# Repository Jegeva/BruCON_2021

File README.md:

BruCON 2021
=
This is the firmware and pcb for brucon badge 

as of released at the conference **ie. including** :

* the mistake that needs a bodge (vbat to the sensor, backlights and leds missing a bit of trace) and 
* the mistake with the connector (don't use the one refed in the kicad docs, it is keyed down instead of up)

Licenses :
=

-my (**ugly**) firmware code and the PCB are CERN-OHL-P

-the gasmask art is CC/NA by Ray Harvey

-Espressif stuff : 
[see here](https://docs.espressif.com/projects/esp-idf/en/latest/esp32/COPYRIGHT.html)

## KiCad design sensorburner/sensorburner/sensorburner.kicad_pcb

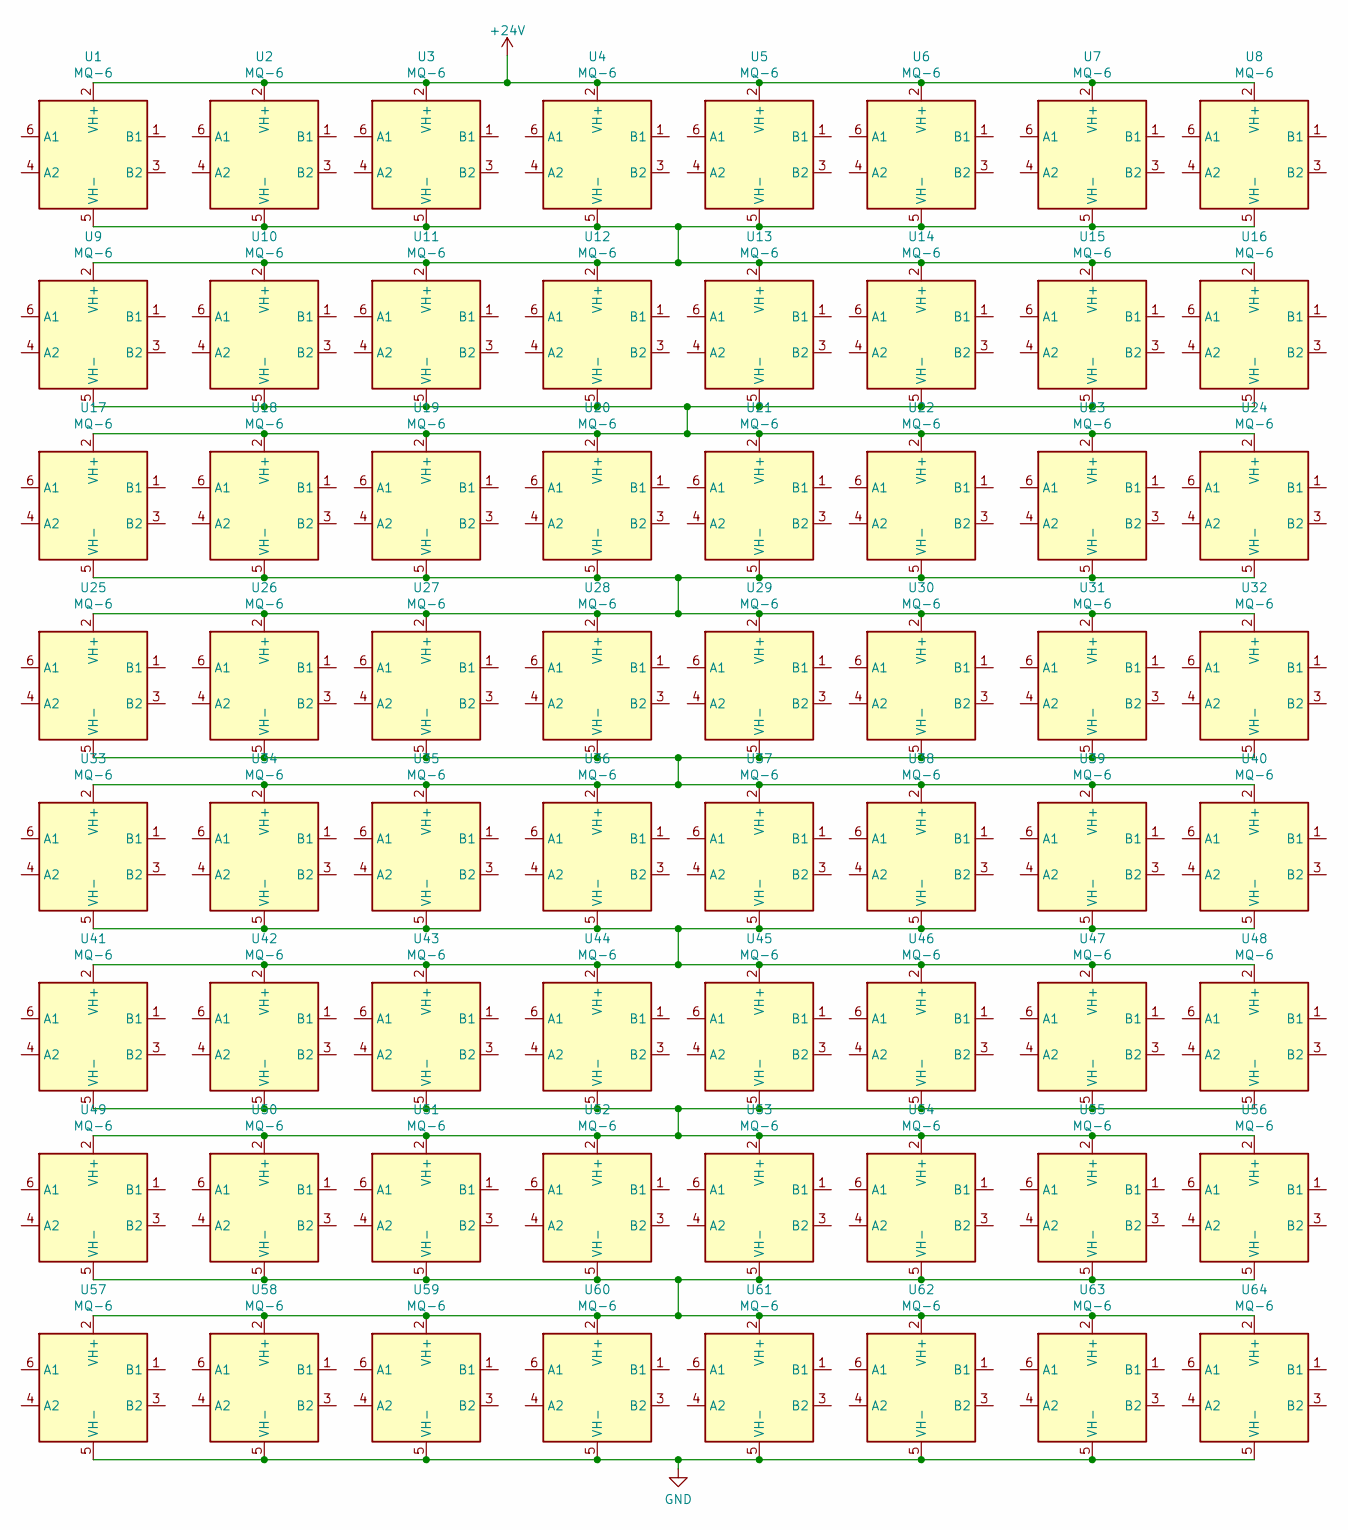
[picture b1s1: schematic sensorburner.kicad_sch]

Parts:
U1, U2, U3, U4, U5, U6, U7, U8, U9, U10, U11, U12, U13, U14, U15, U16, U17, U18, U19, U20, U21, U22, U23, U24, U25, U26, U27, U28, U29, U30, U31, U32, U33, U34, U35, U36, U37, U38, U39, U40, U41, U42, U43, U44, U45, U46, U47, U48, U49, U50, U51, U52, U53, U54, U55, U56, U57, U58, U59, U60, U61, U62, U63, U64: MQ-6; MQ-3-sparkfuntight

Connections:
+24V: U1.2 (VH+), U2.2 (VH+), U3.2 (VH+), U4.2 (VH+), U5.2 (VH+), U6.2 (VH+), U7.2 (VH+), U8.2 (VH+)
GND: U57.5 (VH-), U58.5 (VH-), U59.5 (VH-), U60.5 (VH-), U61.5 (VH-), U62.5 (VH-), U63.5 (VH-), U64.5 (VH-)
unnamed: U1.5 (VH-), U2.5 (VH-), U3.5 (VH-), U4.5 (VH-), U5.5 (VH-), U6.5 (VH-), U7.5 (VH-), U8.5 (VH-), U9.2 (VH+), U10.2 (VH+), U11.2 (VH+), U12.2 (VH+), U13.2 (VH+), U14.2 (VH+), U15.2 (VH+), U16.2 (VH+)
unnamed: U9.5 (VH-), U10.5 (VH-), U11.5 (VH-), U12.5 (VH-), U13.5 (VH-), U14.5 (VH-), U15.5 (VH-), U16.5 (VH-), U17.2 (VH+), U18.2 (VH+), U19.2 (VH+), U20.2 (VH+), U21.2 (VH+), U22.2 (VH+), U23.2 (VH+), U24.2 (VH+)
unnamed: U17.5 (VH-), U18.5 (VH-), U19.5 (VH-), U20.5 (VH-), U21.5 (VH-), U22.5 (VH-), U23.5 (VH-), U24.5 (VH-), U25.2 (VH+), U26.2 (VH+), U27.2 (VH+), U28.2 (VH+), U29.2 (VH+), U30.2 (VH+), U31.2 (VH+), U32.2 (VH+)
unnamed: U25.5 (VH-), U26.5 (VH-), U27.5 (VH-), U28.5 (VH-), U29.5 (VH-), U30.5 (VH-), U31.5 (VH-), U32.5 (VH-), U33.2 (VH+), U34.2 (VH+), U35.2 (VH+), U36.2 (VH+), U37.2 (VH+), U38.2 (VH+), U39.2 (VH+), U40.2 (VH+)
unnamed: U33.5 (VH-), U34.5 (VH-), U35.5 (VH-), U36.5 (VH-), U37.5 (VH-), U38.5 (VH-), U39.5 (VH-), U40.5 (VH-), U41.2 (VH+), U42.2 (VH+), U43.2 (VH+), U44.2 (VH+), U45.2 (VH+), U46.2 (VH+), U47.2 (VH+), U48.2 (VH+)
unnamed: U41.5 (VH-), U42.5 (VH-), U43.5 (VH-), U44.5 (VH-), U45.5 (VH-), U46.5 (VH-), U47.5 (VH-), U48.5 (VH-), U49.2 (VH+), U50.2 (VH+), U51.2 (VH+), U52.2 (VH+), U53.2 (VH+), U54.2 (VH+), U55.2 (VH+), U56.2 (VH+)
unnamed: U49.5 (VH-), U50.5 (VH-), U51.5 (VH-), U52.5 (VH-), U53.5 (VH-), U54.5 (VH-), U55.5 (VH-), U56.5 (VH-), U57.2 (VH+), U58.2 (VH+), U59.2 (VH+), U60.2 (VH+), U61.2 (VH+), U62.2 (VH+), U63.2 (VH+), U64.2 (VH+)

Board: 2 copper layers, 64 parts (0 on the bottom side), 9 nets, no tracks yet.

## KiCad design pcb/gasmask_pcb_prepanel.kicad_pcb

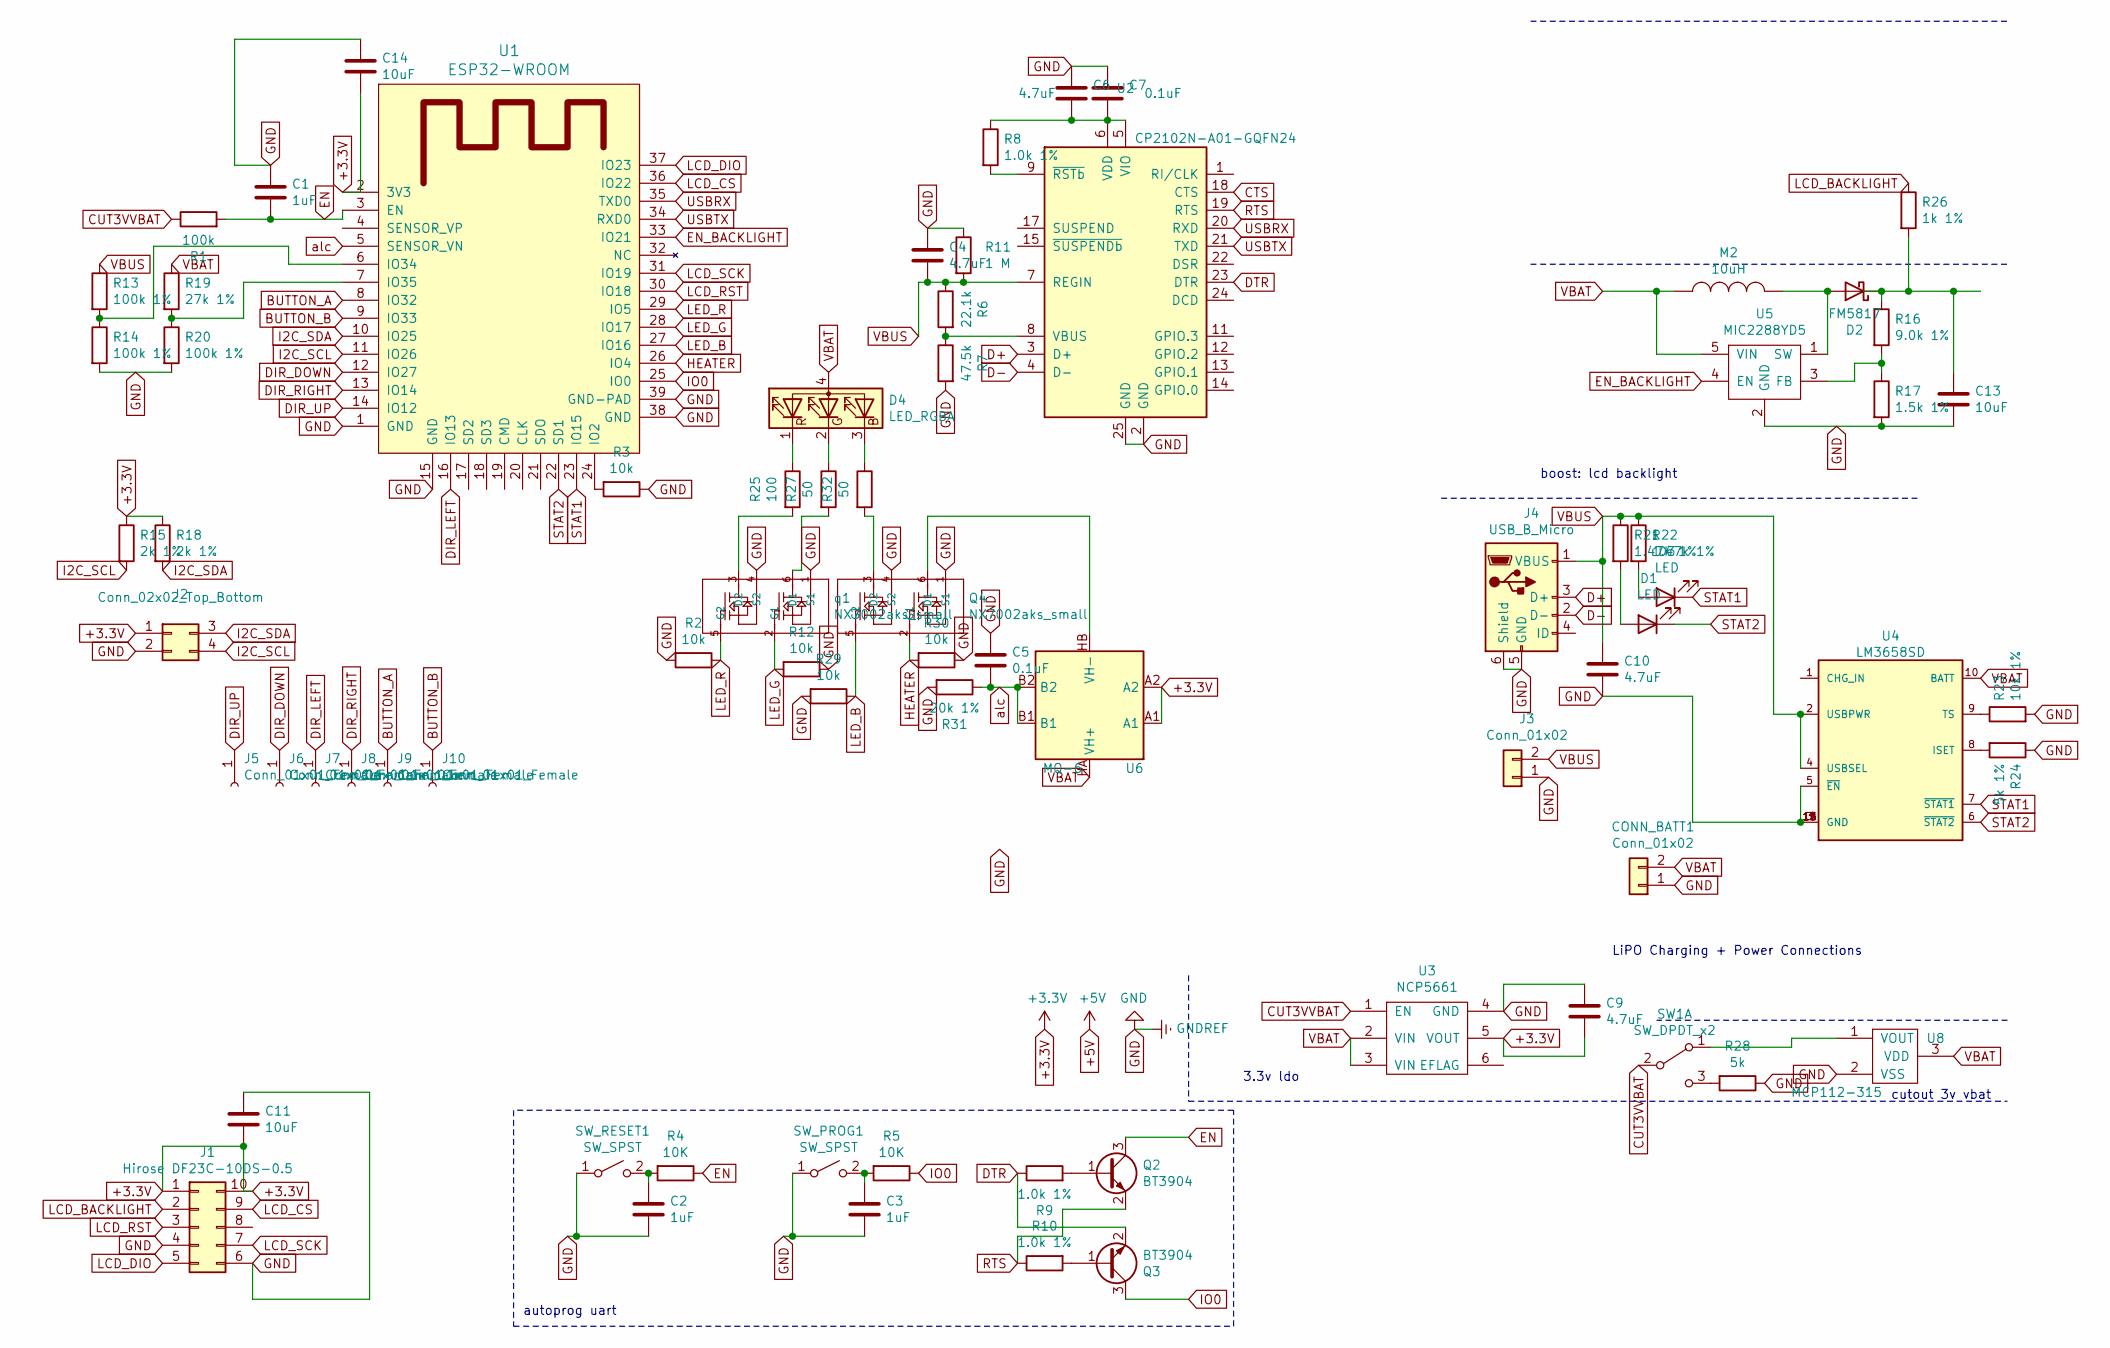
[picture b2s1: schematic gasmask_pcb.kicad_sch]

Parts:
C1, C2, C3: 1uF; C_0805_2012Metric
C4, C6, C9, C10: 4.7uF; C_0805_2012Metric
C5, C7: 0.1uF; C_0805_2012Metric
C11, C13, C14: 10uF; C_0805_2012Metric
CONN_BATT1: Conn_01x02; JST-PH-SM4-TB-2
D1, D3: LED; LED_0603_1608Metric
D2: FM5817; DO-214-FM5817
D4: LED_RGBA; LED_Cree-PLCC4_2x2mm_CW
J1: Hirose DF23C-10DS-0.5; DF23C-10DS-0.5V
J2: Conn_02x02_Top_Bottom; PinHeader_2x02_P2.54mm_Vertical
J3: Conn_01x02; PinHeader_1x02_P2.54mm_Vertical
J4: USB_B_Micro; USB_Micro-B_Molex_47346-0001
J5, J6, J7, J8, J9, J10: Conn_01x01_Female; touch_10mm
M2: 10uH; L_0805_2012Metric
Q2, Q3: BT3904; SOT-23
Q4: NX7002aks_small; SOT-363_SC-70-6
R1: 100k; R_0805_2012Metric
R2, R3, R12, R29, R30: 10k; R_0805_2012Metric
R4, R5: 10K; R_0805_2012Metric
R6: 22.1k; R_0805_2012Metric
R7: 47.5k; R_0805_2012Metric
R8, R9, R10: 1.0k 1%; R_0805_2012Metric
R11: 1 M; R_0805_2012Metric
R13, R14, R20: 100k 1%; R_0805_2012Metric
R15, R18: 2k 1%; R_0805_2012Metric
R16: 9.0k 1%; R_0805_2012Metric
R17: 1.5k 1%; R_0805_2012Metric
R19: 27k 1%; R_0805_2012Metric
R21, R22: 1.47k 1%; R_0805_2012Metric
R23: 10k 1%; R_0805_2012Metric
R24: 5k 1%; R_0805_2012Metric
R25: 100; R_0805_2012Metric
R26: 1k 1%; R_0805_2012Metric
R27, R32: 50; R_0805_2012Metric
R28: 5k; R_0805_2012Metric
R31: 20k 1%; R_0805_2012Metric
SW1: SW_DPDT_x2; JS102000-SAQN
SW_PROG1: SW_SPST; FSM4JSMATR
SW_RESET1: SW_SPST; FSM4JSMATR
U1: ESP32-WROOM
U2: CP2102N-A01-GQFN24; QFN-24-1EP_4x4mm_P0.5mm_EP2.6x2.6mm
U3: NCP5661; DFN6-3.6x2.15mmP0.95
U4: LM3658SD; IC_TPS61087DSCR
U5: MIC2288YD5; SOT-23-5
U6: MQ-6; MQ-3
U8: MCP112-315; SOT-23
q1: NX7002aks_small; SOT-363_SC-70-6

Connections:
+3.3V: C9.2, C11.2, C14.2, J1.1, J1.10, J2.1, R15.1, R18.1, U1.2 (3V3), U3.5 (VOUT), U6.A1, U6.A2
BUTTON_A: J9.1, U1.8 (IO32)
BUTTON_B: J10.1, U1.9 (IO33)
CTS: U2.18 (CTS)
CUT3VVBAT: R1.1, SW1.2 (B), U3.1 (EN)
D+: J4.3 (D+), U2.3 (D+)
D-: J4.2 (D-), U2.4 (D-)
DIR_DOWN: J6.1, U1.12 (IO27)
DIR_LEFT: J7.1, U1.16 (IO13)
DIR_RIGHT: J8.1, U1.13 (IO14)
DIR_UP: J5.1, U1.14 (IO12)
DTR: Q3.2 (E), R9.1, U2.23 (DTR)
EN: C1.2, Q2.3 (C), R1.2, R4.1, U1.3 (EN)
EN_BACKLIGHT: U1.33 (IO21), U5.4 (EN)
HEATER: Q4.2 (G1), R30.2, U1.26 (IO4)
I2C_SCL: J2.4, R15.2, U1.11 (IO26)
I2C_SDA: J2.3, R18.2, U1.10 (IO25)
IO0: Q3.3 (C), R5.1, U1.25 (IO0)
LCD_BACKLIGHT: J1.2, R26.1
LCD_CS: J1.9, U1.36 (IO22)
LCD_DIO: J1.5, U1.37 (IO23)
LCD_RST: J1.3, U1.30 (IO18)
LCD_SCK: J1.7, U1.31 (IO19)
LED_B: Q4.5 (G2), R29.1, U1.27 (IO16)
LED_G: R12.2, U1.28 (IO17), q1.2 (G1)
LED_R: R2.1, U1.29 (IO5), q1.5 (G2)
unnamed: C2.1, R4.2, SW_RESET1.2 (B)
unnamed: C3.1, R5.2, SW_PROG1.2 (B)
unnamed: C6.2, C7.2, R8.1, U2.5 (VIO), U2.6 (VDD)
unnamed: C13.1, D2.1 (K), R16.1, R26.2
unnamed: D1.2 (A), R21.2
unnamed: D2.2 (A), M2.2, U5.1 (SW)
unnamed: D3.2 (A), R22.2
unnamed: D4.1 (RK), R25.1
unnamed: D4.2 (GK), R27.1
unnamed: D4.3 (BK), R32.1
unnamed: Q2.1 (B), R9.2
unnamed: Q3.1 (B), R10.2
unnamed: Q4.3 (D2), R32.2
unnamed: Q4.6 (D1), U6.HB (VH-)
unnamed: R3.2, U1.24 (IO2)
unnamed: R6.2, R7.1, U2.8 (VBUS)
unnamed: R8.2, U2.9 (~RSTb)
unnamed: R13.2, R14.1, U1.6 (IO34)
unnamed: R16.2, R17.1, U5.3 (FB)
unnamed: R19.2, R20.1, U1.7 (IO35)
unnamed: R23.1, U4.9 (TS)
unnamed: R28.2, SW1.3 (C)
unnamed: SW1.1 (A), U8.1 (VOUT)
unnamed: R25.2, q1.3 (D2)
unnamed: R27.2, q1.6 (D1)
RTS: Q2.2 (E), R10.1, U2.19 (RTS)
STAT1: D3.1 (K), U1.23 (IO15), U4.7 (~STAT1)
STAT2: D1.1 (K), U1.22 (SD1), U4.6 (~STAT2)
USBRX: U1.35 (TXD0), U2.20 (RXD)
USBTX: U1.34 (RXD0), U2.21 (TXD)
VBAT: CONN_BATT1.2, D4.4 (A), M2.1, R19.1, U3.2 (VIN), U3.3 (VIN), U4.10 (BATT), U5.5 (VIN), U6.HA (VH+), U8.3 (VDD); also elsewhere on the board
alc: C5.2, R31.1, U1.5 (SENSOR_VN), U6.B1, U6.B2

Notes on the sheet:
autoprog uart
3.3v ldo
boost: lcd backlight
LiPO Charging + Power Connections
cutout 3v vbat

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
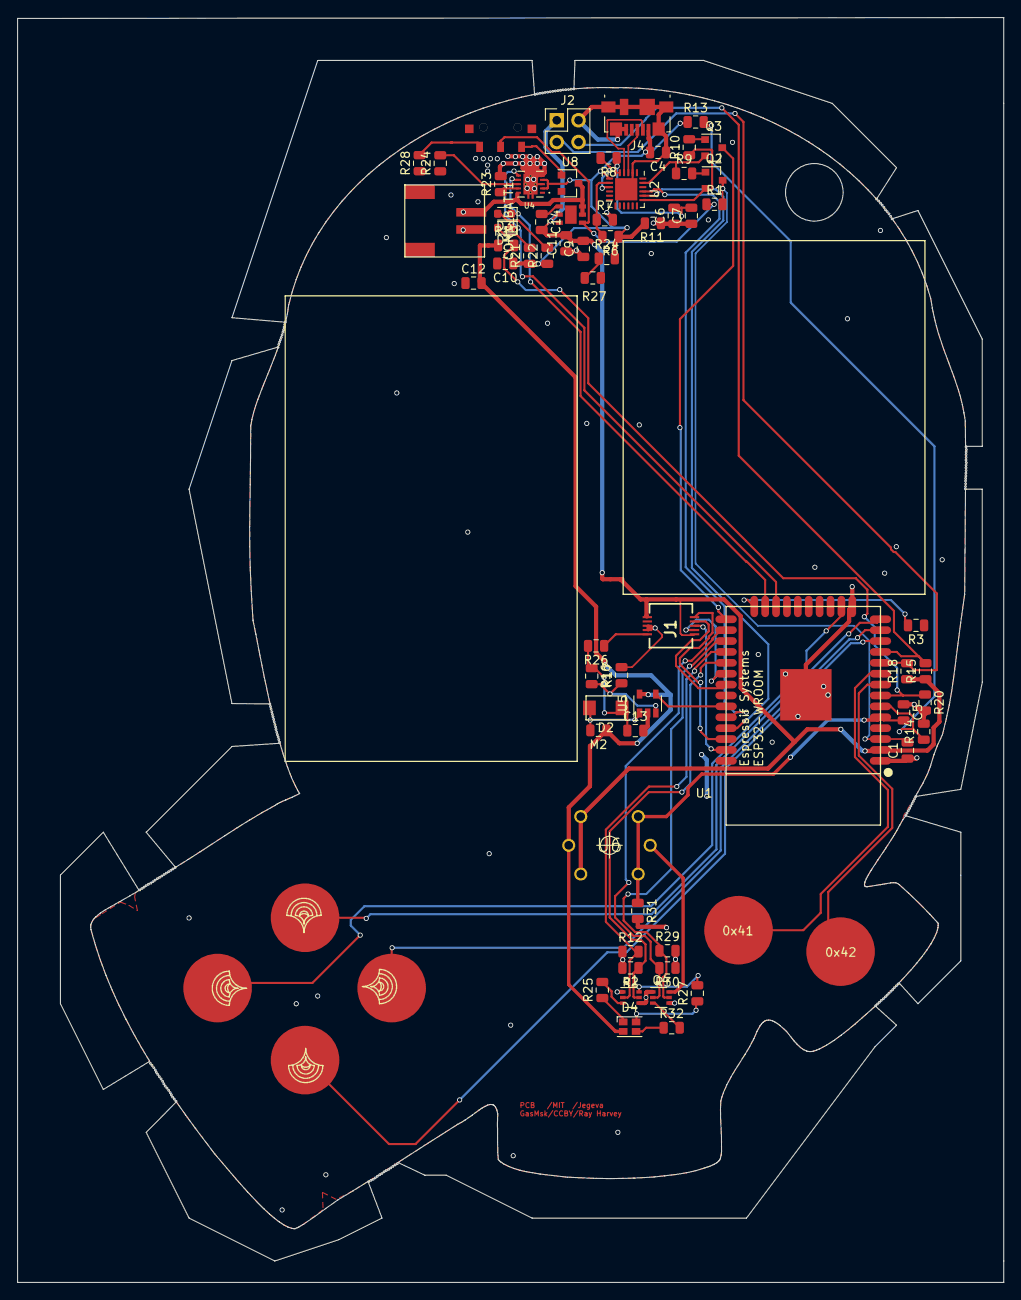
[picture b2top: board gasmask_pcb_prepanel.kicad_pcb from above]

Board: 2 copper layers, 115.0 x 147.5 mm, 70 parts (0 on the bottom side), 59 nets.

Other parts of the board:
C12: 10uF; C_0805_2012Metric
R24#2: 5k 1%; R_0805_2012Metric
R27#2: 10k 1%; R_0805_2012Metric

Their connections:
VBAT: C12.2; also elsewhere on the board

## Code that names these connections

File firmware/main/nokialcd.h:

#ifndef __NOKIA_LCD_H
#define __NOKIA_LCD_H

#include <stdio.h>
#include <stdlib.h>
#include <string.h>
#include <esp32/rom/ets_sys.h>
#include "driver/spi_master.h"
#include "soc/gpio_struct.h"
#include "driver/gpio.h"
#include "battery.h"
#include "math.h"

void MapWestL(void* arg);
void MapNovoL(void* arg);



#define LCD_SCK CONFIG_NOKIA6100_LCD_GPIO_SCK
#define LCD_DIO CONFIG_NOKIA6100_LCD_GPIO_DIO
#define LCD_RST CONFIG_NOKIA6100_LCD_GPIO_RST
#define LCD_CS  CONFIG_NOKIA6100_LCD_GPIO_CS

#define ENSCR_PIN CONFIG_NOKIA6100_LCD_GPIO_BACKLIGHT


#define PIN_BL CONFIG_CROSS_PIN_BUTTON_LEFT
#define PIN_BR CONFIG_CROSS_PIN_BUTTON_RIGHT
#define PIN_BU CONFIG_CROSS_PIN_BUTTON_UP
#define PIN_BD CONFIG_CROSS_PIN_BUTTON_DOWN
#define PIN_BA CONFIG_CROSS_PIN_BUTTON_A
#define PIN_BB CONFIG_CROSS_PIN_BUTTON_B

#define PIN_NCHARGING 34

#define LCD_SCK_L gpio_set_level(LCD_SCK,0)
#define LCD_SCK_H gpio_set_level(LCD_SCK,1)
#define LCD_DIO_L gpio_set_level(LCD_DIO,0)
#define LCD_DIO_H gpio_set_level(LCD_DIO,1)
#define LCD_RST_L gpio_set_level(LCD_RST,0)
#define LCD_RST_H gpio_set_level(LCD_RST,1)
#define LCD_CS_L  gpio_set_level(LCD_CS ,0)
#define LCD_CS_H  gpio_set_level(LCD_CS ,1)

#define dl_us(x)  ets_delay_us(x)
#define clockit   LCD_SCK_L;                    \
    dl_us(1);                                   \
    LCD_SCK_H;

#define EPSON 1
#define PHILLIPS 0

#define LCD_COMMAND 0
#define LCD_DATA 1

// ripped from the arduino library

#define ROW_LENGTH	132
#define COL_HEIGHT	132

//********************************************************************
//					EPSON Controller Definitions
//********************************************************************
#define DISON       0xAF	// Display on
#define DISOFF      0xAE	// Display off
#define DISNOR      0xA6	// Normal display
#define DISINV      0xA7	// Inverse display
#define SLPIN       0x95	// Sleep in
#define SLPOUT      0x94	// Sleep out
#define COMSCN      0xBB	// Common scan direction
#define DISCTL      0xCA	// Display control
#define PASET       0x75	// Page address set
#define CASET       0x15	// Column address set
#define DATCTL      0xBC	// Data scan direction, etc.
#define RGBSET8     0xCE	// 256-color position set
#define RAMWR       0x5C	// Writing to memory
#define RAMRD       0x5D	// Reading from memory
#define PTLIN       0xA8	// Partial display in
#define PTLOUT      0xA9	// Partial display out
#define RMWIN       0xE0	// Read and modify write
#define RMWOUT      0xEE	// End
#define ASCSET      0xAA	// Area scroll set
#define SCSTART     0xAB	// Scroll start set
#define OSCON       0xD1	// Internal oscillation on
#define OSCOFF      0xD2	// Internal osciallation off
#define PWRCTR      0x20	// Power control
#define VOLCTR      0x81	// Electronic volume control
#define VOLUP       0xD6	// Increment electronic control by 1
#define VOLDOWN     0xD7	// Decrement electronic control by 1
#define TMPGRD      0x82	// Temperature gradient set
#define EPCTIN      0xCD	// Control EEPROM
#define EPCOUT      0xCC	// Cancel EEPROM control
#define EPMWR       0xFC	// Write into EEPROM
#define EPMRD       0xFD	// Read from EEPROM
#define EPSRRD1     0x7C	// Read register 1
#define EPSRRD2     0x7D	// Read register 2
#define NOP         0x25	// No op

//********************************************************************
//			PHILLIPS Controller Definitions
//********************************************************************
//LCD Commands
#define	NOPP		0x00	// No operation
#define	BSTRON		0x03	// Booster voltage on
#define SLEEPIN     0x10	// Sleep in
#define	SLEEPOUT	0x11	// Sleep out
#define	NORON		0x13	// Normal display mode on
#define	INVOFF		0x20	// Display inversion off
#define INVON      	0x21	// Display inversion on
#define	SETCON		0x25	// Set contrast
#define DISPOFF     0x28	// Display off
#define DISPON      0x29	// Display on
#define CASETP      0x2A	// Column address set
#define PASETP      0x2B	// Page address set
#define RAMWRP      0x2C	// Memory write
#define RGBSET	    0x2D	// Color set
#define	MADCTL		0x36	// Memory data access control
#define	PCOLMOD		0x3A	// Interface pixel format
#define DISCTR      0xB9	// Super frame inversion
#define	EC			0xC0	// Internal or external oscillator

//*******************************************************
//				12-Bit Color Definitions
//*******************************************************
#define B12_BLACK	    0xF000
#define B12_NAVY 		0xF008
#define B12_BLUE		0xF00F
#define B12_TEAL 		0xF088
#define B12_EMERALD		0xF0C5
#define	B12_GREEN		0xF0F0
#define B12_CYAN		0xF0FF
#define B12_SLATE 		0xF244
#define B12_INDIGO  	0xF408
#define B12_TURQUOISE	0xF4ED
#define B12_OLIVE 		0xF682
#define B12_MAROON 		0xF800
#define B12_PURPLE 		0xF808
#define B12_GRAY 		0xF888
#define B12_SKYBLUE		0xF8CE
#define B12_BROWN		0xFB22
#define B12_CRIMSON 	0xFD13
#define B12_ORCHID 		0xFD7D
#define B12_RED			0xFF00
#define B12_MAGENTA		0xFF0F
#define B12_ORANGE 		0xFF40
#define B12_PINK		0xFF6A
#define B12_CORAL 		0xFF75
#define B12_SALMON 		0xFF87
#define B12_GOLD 		0xFFD0
#define B12_YELLOW		0xFFF0
#define B12_WHITE		0xFFFF

//*******************************************************
//                              Circle Definitions
//*******************************************************
#define FULLCIRCLE 1
#define OPENSOUTH  2
#define OPENNORTH  3
#define OPENEAST   4
#define OPENWEST   5
#define OPENNORTHEAST 6
#define OPENNORTHWEST 7
#define OPENSOUTHEAST 8
#define OPENSOUTHWEST 9
#define FILL 0
#define ESE 1
#define ENE 2
#define WSW 3
#define WNW 4
#define SSE 5
#define NNE 6
#define SSW 7
#define NNW 8

#define ROW_LENGTH	132
#define COL_HEIGHT	132

void init_lcd(int type);
void switchbacklight(int state);
void lcd_clearB12(uint16_t color);

void lcd_contrast(char setting);
void lcd_setArc(int x0, int y0, int radius, int arcSegments[], int numSegments, int lineThickness, int color);
void lcd_setCircle (int x0, int y0, int radius, int color, int lineThickness);
void lcd_setChar(char c, int x, int y, int fColor, int bColor, char uselastfill);
void lcd_setStr(char *pString, int x, int y, int fColor, int bColor, char uselastfill, char newline);
void lcd_setLine(int x0, int y0, int x1, int y1, int color);
void lcd_setRect(int x0, int y0, int x1, int y1, unsigned char fill, int color);
void lcd_printLogo(void);
void lcd_printBMP(char * image_main); //prints an image (BMP);
void lcd_off(void);
void lcd_on(void);
void lcd_sync(void);
void bruconlogo();

typedef uint16_t pixel_t;

typedef struct image_s {
    int w;
    int h;
    pixel_t buffer[];
} image_t;

void draw_pixel(int x, int y, pixel_t color, unsigned int blend);
void draw_image(const image_t * img, int x, int y);
uint32_t VivaLaVodkaL(void* arg);

typedef struct {
    const uint16_t * data;
    const uint16_t * lookup;
    const uint16_t height;
    const uint16_t min;
    const uint16_t max;
} font_t;

typedef struct {
    uint16_t h;
    uint16_t w;
    int16_t left;
    int16_t top;
    int16_t advance;
    uint16_t buffer[];
} font_char_t;

int string_width(const font_t * font, const char * str);
void draw_string(const font_t * font, int x, int y, pixel_t color, const char * str);

#define LEFT     0x00000001
#define CENTER   0x00000002
#define RIGHT    0x00000003
#define NOKIA_ALIGN_H  0x0000000F

#define TOP      0x00000010
#define VCENTER  0x00000020
#define BOTTOM   0x00000030
#define NOKIA_ALIGN_V  0x000000F0

#define WRAP     0x00000100

void draw_string_aligned(const font_t * font, int x, int y, int w, int h,
        pixel_t color, unsigned int flags, const char *str);

extern volatile char preventbacklighttimeoutTask ;

#endif

// vim: expandtab:ts=4:sw=4

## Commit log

2021-10-19 as of the con
2021-10-19 readme
